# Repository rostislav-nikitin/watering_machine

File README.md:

# Watering machine

Watering machine is a device that control a watering of the garden. This particular machine provides sequential zones watering. This was made to avoid low watering pressure that can happens in case of the parallel mode zone watering.

This device is a control unit with outputs to the external valves - one per watering zone.

<!-- -->

## Modes
The device is designed to work in a two primary modes.

**Normal watering mode**

Used for the regular day-by-day watering. Each zone watering time interval set by the particular zone settings.

**Service mode**

Used for the system blowing before the coservation.
Usually in this mode pump provides an air instead of water. In this case switching to the next zone should be done manually. Through the control button/external input instead of zones watering interval time settings.

According to this, some of button has a different functions depends on the current mode and device state.

## Device logical structure
* [PCB 3D view](#pcb-3d-view "PCB 3D view")
* [Inputs](#Inputs "Inputs")
    * [Power inputs](#power-inputs "Power inputs")
	    * [Main power input](#main-power-input "Main power input")
		    * [Internal low-voltage circuits powering](#internal-low-voltage-circuits-powering "Internal low-voltage circuits powering")
            * [Valves powering](#valves-powering "Valves powering")
        * [Batteries bay](#batteries-bay "Batteries bay")
    * [Logical inputs](#logical-inputs "Logical inputs")
	    * [Control buttons](#control-buttons "Control buttons")
	    * [24 hours internal timer](#24-hours-internal-timer "24 hours internal timer")
	    * [External inputs](#external-inputs)
	        * [External TTL-levels input](#external-ttl-levels-input "External TTL-levels input")
		    * [External rain sensor input](#external-rain-sensor-input "External rain sensor input")
* [Outputs](#outputs "Outputs")
	* [State indicators](#state-indicators "State indicators")
	* [Valves outputs](#valves-outputs "Valves outputs")
	* [Cascading output (not implemented yet)](#cascading-output "Cascading output (not implemented yet)")

## PCB 3D view

<!--  -->

## Inputs

### Power inputs

#### Main power input

This device can be powered by the 9-36 VAC / 500 mA+ power supply.
Power supply characteristics should be calculated by a next formula:

Power supply voltage = valve voltage. Accepted range: [9 VAC - 36 VAC].

Power supply minimal current = 500 mA (internal circuits) + valve maximal current. Accepterd range: [500 mA - 2 A].

##### Internal low-voltage circuits powering
To power input low-voltage circuits was used primary power supply through current rectification and stabilisation. There is +5 VDC powering used for the low-voltage TTL circuits.
* U = +5 VDC (+/- 5%)
* I <= 700 mA

##### Valves powering
Valves solenoids are powering directly from the [main power input](#main-power-input "Main power input") through triacs without any stabilization or transformation.

#### Batteries bay
Battery powering is consists of the battery bay & controller which control charge level/charge batteries. It powers only chips required to run internal time and store device 24 hours timer state. Because they should be invariant for the external power outages.
Ther was used battery bay for 2x18650 battries. Bacause each battery voltage is 3.8-4.2 VDC. And if they are connected sequetely then they provides ~8 VDC voltage. Which is enough to provide +5 VDC after the stabilization.

### Logical inputs

#### Control buttons
Control buttons should be used to set the current watering mode, zone watering time intervals and change the device state - start, stop watering, switch to the next zone manually.

##### Mode switch button

This button toggle normal watering mode / service mode.

##### Start/Stop/Next button

_In the normal watering mode_

In this mode Start/Stop/Next button works in a Start/Stop toggle mode. When device not in a progress state and rain sensor circuit is disonnected then it start watering. Otherwise if device is in progress then stop.

_In the serivce mode_

In this mode Start/Stop/Next button works in a Start->Next->Stop mode. When watering is stopped then this button starts it in case rain sensor circuit is disconnected. On the next push it switch watering zone to the next one. On push when the last zone is in progress it stops the watering.

##### Timer On/Off switch button

This button toggle [24 hours internal timer](#24-hours-internal-timer "24 hours internal timer") on/off.

##### Zone watering time interwal switch

Each zone watering time can be set with a 3 minutes percision.

There are 2 x 5-position sliding switches per zone. One for the rough setup and one for the fine setup. The total zone watering time interval is a sum of rough and fine values.

_Rough setup 5-position sliding switch_

Positions: [1] - 0 minutes, [2] - 15 minutes, [3] - 30 minutes, [4] - 45 minutes, [5] - 60 minutes

_Fine setup 5-position sliding switch_

Positions: [1] - 0 minutes, [2] - 3 minutes, [3] - 6 minutes, [4] - 9 minutes, [5] - 12 minutes

Example: If rough switch in a position [3] (30 minutes) and fine switch in a position [4] (9 minutes) then zone time interval is equal to the  30 minutes + 9 minutes = 39 minutes

#### 24 hours internal timer
24 hours internal timer is used to start watering each 24 hours with everyday recuring.

Timer On/Off button toggle timer function.

##### Watering start time setup
Watering start time could be setup only in normal watering model. This can be made through a manual start watering by the pressing a start/stop/next or by external TTL-levels input high signal. And after the 24 hours it will starts watering again if device is not in a progress state and rain sensor circuit is disconnected.

#### External inputs

##### External TTL-levels input
The external TTL-levels input behaviour is a same as [Start/Stop/Next button](#start/stop/next-button "Start/Stop/Next button") behaviour. Each high TTL level toggle watering state depends on the current mode and the rain sensor circuit conection state.

##### External rain sensor input
It can be used to connect external rain sensor. Rain sensor shold connect both connector pins on rain begins and disconnect on rain ends. When pins are connected then watering is blocking with a maximal priority - no one signal can start watering.
If it connects pins when watering was is in progress then watering stops. And starts only when next start signal comes in case if rain sensor connector pins will be disconnected. 

## Outputs

### State indicators
* Power indicator: 
    * Off if device powered off
    * On if device is powered on
* Mode indicator: 
    * Off if device is in normal watering mode
    * On if device is in service mode
* In progress indicator:
    * Off if device in suspend mode (waiting for the start watering signal)
    * On if watering is in progress
* Zone watering in progress indicator. Each zone has own it's one:
    * Off if a current zone watering not is in progress state
    * On if a current zone watering is in progress state
* Rain indicator:
    * Off if rain sensor circuit is disconnected
    * On if rain sensor circuit is connected
* Change battery indicator:
    * Off if battery in a good state
    * Flashes if battery is corrupted and need replacement

### Valves outputs
There are ouptuts with [valves powering](#valves-powering "Valves powering"). At the moment only one output is active, according to the current watering zone.

### Cascading output
On last zone watering finish there is raises short high-level TTL impulse to cascade next watering device in watering devices sequence.

## Links
Watering machine intro and description on my YouTube channel:

## Contacts
e-mail: rostislav.nikitin@gmail.com

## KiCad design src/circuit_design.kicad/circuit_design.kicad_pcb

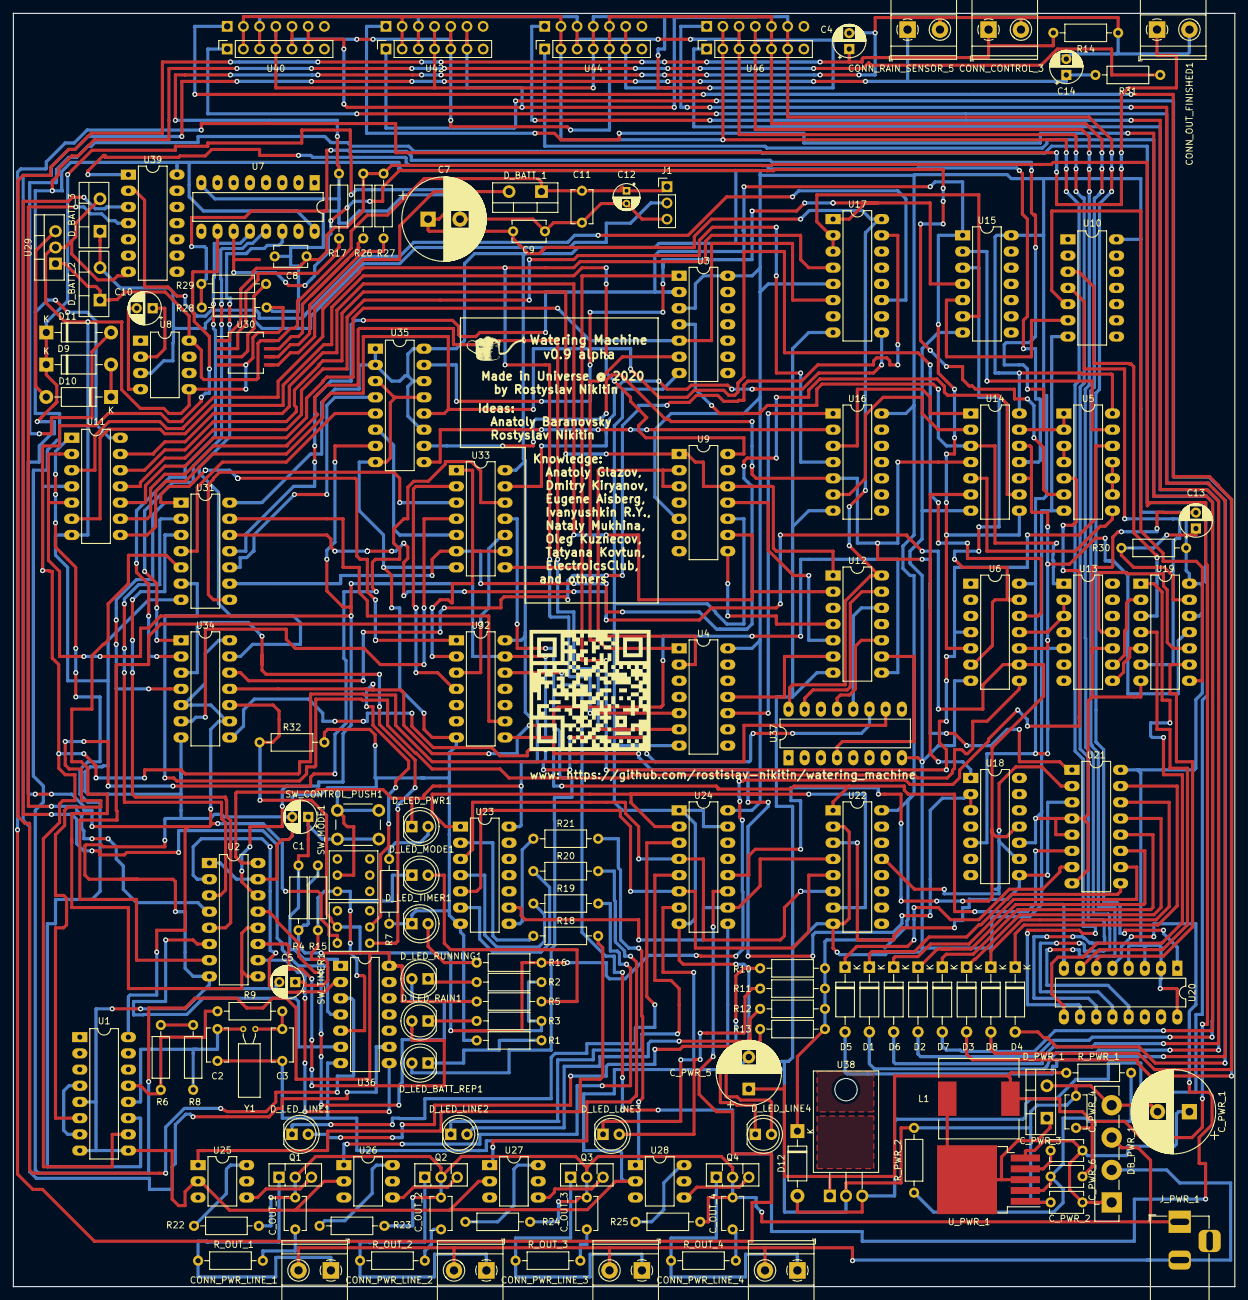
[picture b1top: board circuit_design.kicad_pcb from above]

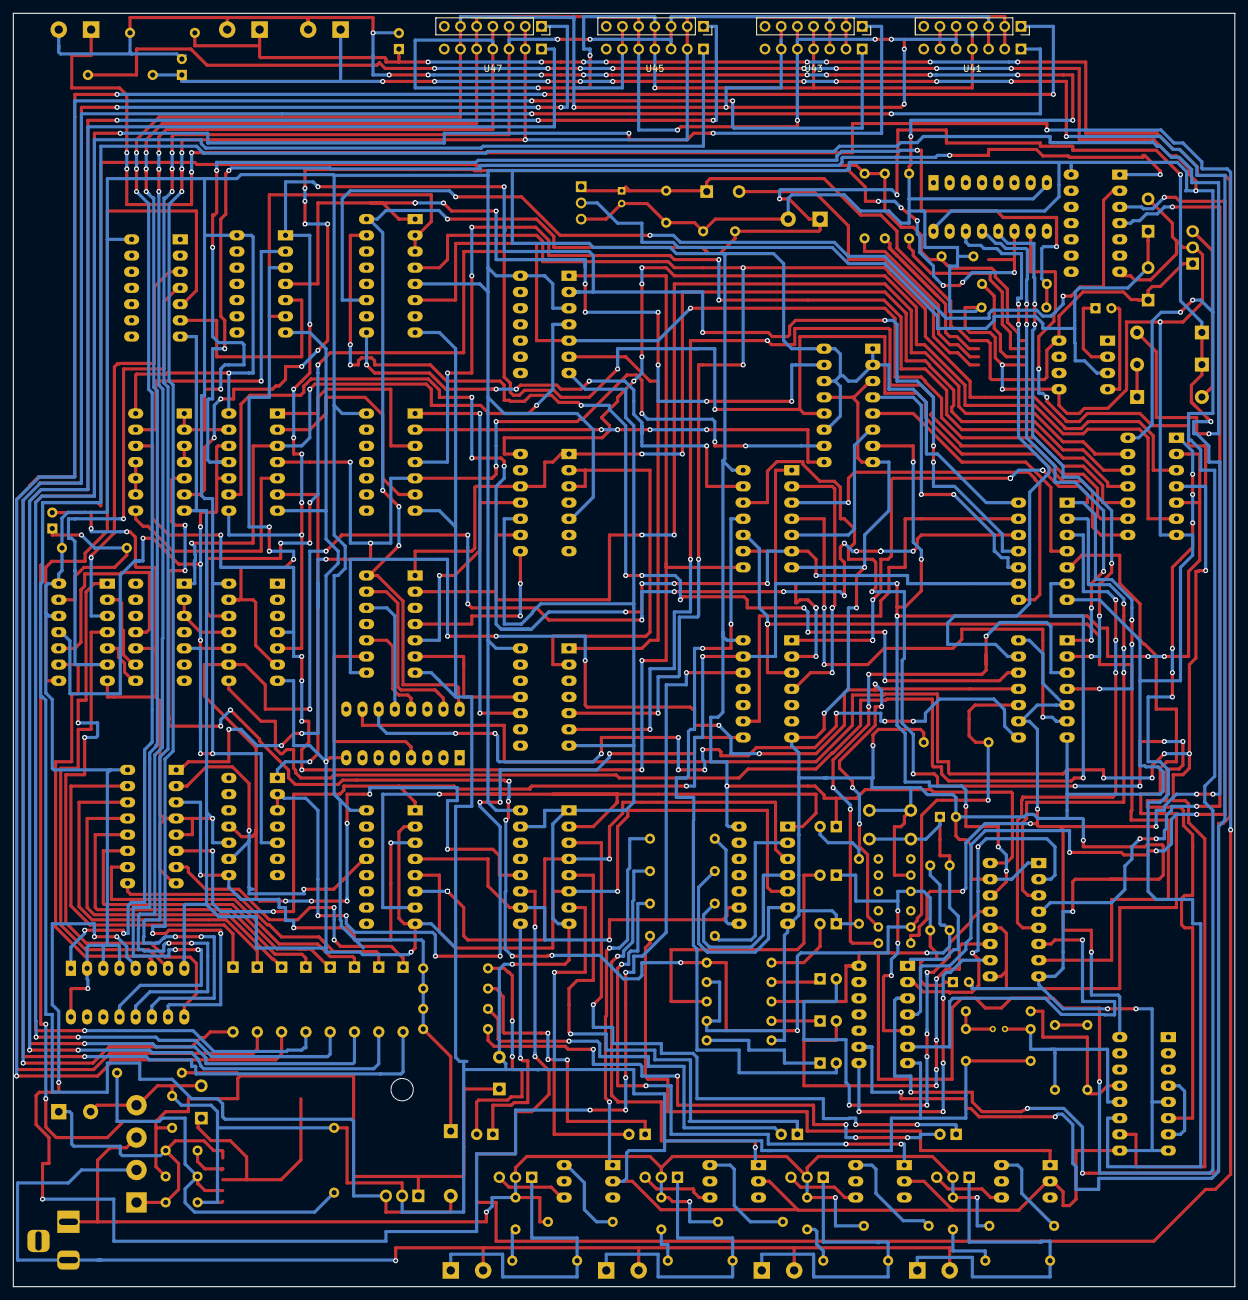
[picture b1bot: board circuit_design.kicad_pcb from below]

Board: 2 copper layers, 191.5 x 199.6 mm, 154 parts (4 on the bottom side), 186 nets.

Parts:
C1, C4, C5, C13, C14: 100uF; CP_Radial_D5.0mm_P2.50mm
C2: 62pF; C_Disc_D5.1mm_W3.2mm_P5.00mm
C3: 22pF; C_Disc_D5.1mm_W3.2mm_P5.00mm
C7: 1000uF; CP_Radial_D13.0mm_P5.00mm
C8, C11: 100nF; C_Disc_D5.1mm_W3.2mm_P5.00mm
C9: 105; C_Disc_D5.1mm_W3.2mm_P5.00mm
C10: 10uF/16V; CP_Radial_D5.0mm_P2.50mm
C12: 22uF/16V; CP_Radial_D4.0mm_P2.00mm
CONN_CONTROL_3: Conn_01x02_Male; TerminalBlock_Phoenix_MKDS-1,5-2-5.08_1x02_P5.08mm_Horizont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
CONN_OUT_FINISHED1: Conn_01x02_Male; TerminalBlock_Phoenix_MKDS-1,5-2-5.08_1x02_P5.08mm_Horizont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
CONN_PWR_LINE_1, CONN_PWR_LINE_2, CONN_PWR_LINE_3, CONN_PWR_LINE_4: Conn_01x02_Male; TerminalBlock_Phoenix_MKDS-1,5-2-5.08_1x02_P5.08mm_Horizont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
CONN_RAIN_SENSOR_5: Conn_01x02_Male; TerminalBlock_Phoenix_MKDS-1,5-2-5.08_1x02_P5.08mm_Horizont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
C_OUT_1, C_OUT_2, C_OUT_3, C_OUT_4: 103; C_Disc_D5.1mm_W3.2mm_P5.00mm
C_PWR_1: 1000 uF/50V; CP_Radial_D13.0mm_P5.00mm
C_PWR_2, C_PWR_3, C_PWR_4: 105; C_Disc_D5.1mm_W3.2mm_P5.00mm
C_PWR_5: 330 uF/50V; CP_Radial_D10.0mm_P5.00mm
C_PWR_6: 333; C_Disc_D5.1mm_W3.2mm_P5.00mm
D1, D2, D3, D4, D5, D6, D7, D8: 1N5817; D_A-405_P10.16mm_Horizontal
D9, D11, D12: 1N4007; D_DO-41_SOD81_P10.16mm_Horizontal
D10: 1N5817; D_DO-41_SOD81_P10.16mm_Horizontal
DB_PWR_1: RS207; Diode_Bridge_Vishay_GBL
D_BATT_1, D_BATT_2, D_BATT_3: SS24T3G; TO-220-2_Vertical
D_LED_BATT_REP1: LED; LED_D5.0mm
D_LED_LINE1, D_LED_LINE2, D_LED_LINE3, D_LED_LINE4: LED; LED_D5.0mm
D_LED_MODE1: LED; LED_D5.0mm
D_LED_PWR1: LED; LED_D5.0mm
D_LED_RAIN1: LED; LED_D5.0mm
D_LED_RUNNING1: LED; LED_D5.0mm
D_LED_TIMER1: LED; LED_D5.0mm
D_PWR_1: MBR745; TO-220-2_Vertical
J1: CONN_BAT; PinHeader_1x03_P2.54mm_Vertical
J_PWR_1: Barrel_Jack; BarrelJack_Horizontal
L1: 47 uH/5A; L_12x12mm_H6mm
Q1, Q2, Q3, Q4: BT134-600E; TO-126-3_Vertical
R1: 200; R_Axial_DIN0207_L6.3mm_D2.5mm_P10.16mm_Horizontal
R2, R3, R5, R7, R10, R11, R12, R13: 270Ohm; R_Axial_DIN0207_L6.3mm_D2.5mm_P10.16mm_Horizontal
R4, R14, R15, R22, R23, R24, R25, R31: 1KOhm; R_Axial_DIN0207_L6.3mm_D2.5mm_P10.16mm_Horizontal
R6, R8: 10MOhm; R_Axial_DIN0207_L6.3mm_D2.5mm_P10.16mm_Horizontal
R9: 510KOhm; R_Axial_DIN0207_L6.3mm_D2.5mm_P10.16mm_Horizontal
R16: 270; R_Axial_DIN0207_L6.3mm_D2.5mm_P10.16mm_Horizontal
R17, R27, R30: 10K; R_Axial_DIN0207_L6.3mm_D2.5mm_P10.16mm_Horizontal
R18, R19, R20, R21: 100 Ohm; R_Axial_DIN0207_L6.3mm_D2.5mm_P10.16mm_Horizontal
R26: 0.5R; R_Axial_DIN0207_L6.3mm_D2.5mm_P10.16mm_Horizontal
R28: 500R; R_Axial_DIN0207_L6.3mm_D2.5mm_P10.16mm_Horizontal
R29: 400R; R_Axial_DIN0207_L6.3mm_D2.5mm_P10.16mm_Horizontal
R32: 1 KOhm; R_Axial_DIN0207_L6.3mm_D2.5mm_P10.16mm_Horizontal
R_OUT_1, R_OUT_2, R_OUT_3, R_OUT_4: 39; R_Axial_DIN0207_L6.3mm_D2.5mm_P10.16mm_Horizontal
R_PWR_1: 15K; R_Axial_DIN0207_L6.3mm_D2.5mm_P10.16mm_Horizontal
R_PWR_2: 2.4 K; R_Axial_DIN0207_L6.3mm_D2.5mm_P10.16mm_Horizontal
SW_CONTROL_PUSH1: SW_DPST_x2; SW_PUSH_6mm
SW_MODE1: SW_DPDT_x2; PB22E09
SW_TIMER1: SW_DPDT_x2; PB22E09
U1: К176ИЕ12; DIP-16_W7.62mm_LongPads
U2, U24: К155ЛП10; DIP-16_W7.62mm_LongPads
U3: К155ЛЕ3; DIP-14_W7.62mm_LongPads
U4, U15, U23, U32, U39: К155ЛН1; DIP-14_W7.62mm_LongPads
U5: К155ЛА3; DIP-14_W7.62mm_LongPads
U6, U14: К155ЛЛ1; DIP-14_W7.62mm_LongPads
U7, U37: 4020; DIP-16_W7.62mm_LongPads
U8: ICL7660; DIP-8_W7.62mm_LongPads
U9, U13, U18: К155ИЕ5; DIP-14_W7.62mm_LongPads
U10, U34: К155ЛА4; DIP-14_W7.62mm_LongPads
U11, U16, U33: К155ЛИ1; DIP-14_W7.62mm_LongPads
U12: К155ЛА1; DIP-14_W7.62mm_LongPads
U17, U35: К155ТВ15; DIP-16_W7.62mm_LongPads
U19: К155ЛП5; DIP-14_W7.62mm_LongPads
U20: К155ИВ1; DIP-16_W7.62mm_LongPads
U21: К155ИД7; DIP-16_W7.62mm_LongPads
U22: К155ИД4; DIP-16_W7.62mm_LongPads
U25, U26, U27, U28: MOC3062M; DIP-6_W7.62mm_LongPads
U29: LM7806_TO220; TO-220-3_Vertical
U30: SC6038; SO-8_5.3x6.2mm_P1.27mm
U31: К155ЛЕ1; DIP-14_W7.62mm_LongPads
U36: К155ТЛ2; DIP-14_W7.62mm_LongPads
U38: LM7806_TO220; TO-220-3_Horizontal_TabDown
U40, U41, U42, U43, U44, U45, U46, U47: SPFT_Sliding_Switch; PinSocket_1x07_P2.54mm_Vertical
U_PWR_1: XL4015; TO-263-5_TabPin3
Y1: 32768; Crystal_C38-LF_D3.0mm_L8.0mm_Horizontal

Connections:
+5V: D12.1, D_LED_PWR1.1, R4.1, R5.1, R10.2, R11.2, R12.2, R13.2, R15.1, R30.1, R31.1, U2.16, U3.3, U3.14, U4.14, U5.14, U6.14, U7.16, U9.5, U10.14, U11.14, U13.5, U14.14, U15.14, U16.14, U17.5, U18.5, U19.12, U19.14, U20.2, U20.3, U20.4, U20.16, U21.16, U22.16, U23.14, U24.16, U31.14, U32.14, U33.14, U35.1, U35.2, U35.11, U35.14, U35.16, U36.14, U39.14
+9V: C8.1, C_PWR_4.1, C_PWR_5.1, C_PWR_6.1, L1.2, R26.1, R27.1, R_PWR_1.1, U30.1, U38.1
/Comparison.Equal: U15.6, U17.2, U17.3
/Completed(In): U6.8, U31.6
/Conn_Control_Raw: C4.1, CONN_CONTROL_3.1, R14.1, U36.3
/Control(Ext.2): U2.4, U39.4
/Control(Ext.): U2.2, U36.2
/Control(In1): U2.3, U31.2
/Control(In2): U2.5, U31.3
/D0: U20.10, U40.2, U41.2, U42.2, U43.2, U44.2, U45.2, U46.2, U47.2
/D1: U20.11, U40.3, U41.3, U42.3, U43.3, U44.3, U45.3, U46.3, U47.3
/D2: U20.12, U40.4, U41.4, U42.4, U43.4, U44.4, U45.4, U46.4, U47.4
/D3: U20.13, U40.5, U41.5, U42.5, U43.5, U44.5, U45.5, U46.5, U47.5
/D4: U20.1, U40.6, U41.6, U42.6, U43.6, U44.6, U45.6, U46.6, U47.6
/Mem.Comparison.Equal: U3.5, U11.10, U17.6
/Mode(Ext.): U2.6, U36.6
/Mode(In): U2.7, U32.3, U33.10
/Mode_Raw: C5.1, D_LED_MODE1.1, R15.2, SW_MODE1.3, U36.5
/Next(Out): U3.1, U5.12, U6.4, U33.8
/Rain(In): U2.9, U2.12, U31.5
/Rain(Led): D_LED_RAIN1.2, U2.11
/Rain_Sensor(Ext.): U2.10, U36.8
/Rain_Sensor_Raw: C14.1, CONN_RAIN_SENSOR_5.1, R31.2, U36.9
/Reset(Out): U3.2, U6.5, U14.8, U15.1, U31.11
/Running(Led): D_LED_RUNNING1.2, U2.13
/Running(Out): U2.14, U11.2, U11.5, U21.6, U22.1, U32.13, U35.7
/RunningInv(out): U20.5, U32.12
/Timer.End: U3.4, U13.1, U14.3
BATT_OUT_+: C11.1, C12.1, D_BATT_1.1, D_BATT_2.1, J1.1, U8.8, U29.1, U30.8
BATT_OUT_MID: D_BATT_2.2, D_BATT_3.1, J1.2, U8.3
CLK_MIN: U1.10, U7.10, U11.4, U37.10
CLK_SEC: U1.6, U33.12
Finished: U6.9, U18.11, U24.12, U31.12
GND: C1.2, C2.2, C3.2, C4.2, C5.2, C7.2, C8.2, C9.2, C11.2, C12.2, C13.2, C14.2, CONN_CONTROL_3.2, CONN_OUT_FINISHED1.2, CONN_RAIN_SENSOR_5.2, C_PWR_1.2, C_PWR_2.2, C_PWR_4.2, C_PWR_5.2, DB_PWR_1.4, D_BATT_3.2, D_LED_TIMER1.1, D_PWR_1.2, J1.3, R1.1, R2.2, R3.2, R7.2, R14.2, R17.2, R28.1, R32.2, R_PWR_2.2, SW_CONTROL_PUSH1.1, SW_MODE1.2, U1.5, U1.8, U1.9, U2.1, U2.8, U2.15, U3.7, U4.7, U5.7, U6.7, U7.8, U8.5, U9.10, U10.7, U11.7, U12.7, U13.10, U14.7, U15.7, U16.7, U17.8, U18.10, U19.7, U20.8, U21.4, U21.5, U21.8, U22.2, U22.8, U23.7, U24.1, U24.8, U24.15, U25.2, U26.2, U27.2, U28.2, U29.2, U30.4, U31.7, U32.7, U33.7, U34.7, U35.3, U35.8, U35.13, U36.7, U37.8, U38.2, U39.7, U_PWR_1.1
GNDREF: CONN_PWR_LINE_1.2, CONN_PWR_LINE_2.2, CONN_PWR_LINE_3.2, CONN_PWR_LINE_4.2, DB_PWR_1.2, J_PWR_1.2
Init: U6.10, U14.10, U14.12, U19.11
unnamed: C1.1, R4.2, SW_CONTROL_PUSH1.2, U36.1
unnamed: C2.1, R8.2, U1.12, Y1.1
unnamed: C3.1, R9.1, Y1.2
unnamed: C10.1, U8.2
unnamed: C10.2, U8.4
unnamed: C13.1, R30.2, U19.13
unnamed: CONN_OUT_FINISHED1.1, U24.11
unnamed: CONN_PWR_LINE_1.1, Q1.1, R_OUT_1.2
unnamed: CONN_PWR_LINE_2.1, Q2.1, R_OUT_2.2
unnamed: CONN_PWR_LINE_3.1, Q3.1, R_OUT_3.2
unnamed: CONN_PWR_LINE_4.1, Q4.1, R_OUT_4.2
unnamed: C_OUT_1.2, R_OUT_1.1
unnamed: C_OUT_2.2, R_OUT_2.1
unnamed: C_OUT_3.2, R_OUT_3.1
unnamed: C_OUT_4.2, R_OUT_4.1
unnamed: C_PWR_1.1, C_PWR_2.1, C_PWR_3.1, DB_PWR_1.1, U_PWR_1.5
unnamed: C_PWR_3.2, U_PWR_1.4
unnamed: C_PWR_6.2, R_PWR_1.2, R_PWR_2.1, U_PWR_1.2
unnamed: D1.1, U21.9
unnamed: D1.2, U46.1
unnamed: D2.1, U21.11
unnamed: D2.2, U44.1
unnamed: D3.1, U21.13
unnamed: D3.2, U42.1
unnamed: D4.1, U21.15
unnamed: D4.2, U40.1
unnamed: D5.1, U21.7
unnamed: D5.2, U47.1
unnamed: D6.1, U21.10
unnamed: D6.2, U45.1
unnamed: D7.1, U21.12
unnamed: D7.2, U43.1
unnamed: D8.1, U21.14
unnamed: D8.2, U41.1
unnamed: D9.2, D10.1
unnamed: D10.2, U29.3
unnamed: D11.2, D12.2, U38.3
unnamed: D_BATT_1.2, U30.5
unnamed: D_LED_BATT_REP1.1, R1.2
unnamed: D_LED_BATT_REP1.2, U33.11
unnamed: D_LED_LINE1.1, U24.3
unnamed: D_LED_LINE1.2, R13.1
unnamed: D_LED_LINE2.1, U24.5
unnamed: D_LED_LINE2.2, R12.1
unnamed: D_LED_LINE3.1, U24.7
unnamed: D_LED_LINE3.2, R11.1
unnamed: D_LED_LINE4.1, U24.9
unnamed: D_LED_LINE4.2, R10.1
unnamed: D_LED_MODE1.2, R5.2
unnamed: D_LED_PWR1.2, R7.1
unnamed: D_LED_RAIN1.1, R3.1
unnamed: D_LED_RUNNING1.1, R2.1
unnamed: D_LED_TIMER1.2, R16.2
unnamed: D_PWR_1.1, L1.1, U_PWR_1.3
unnamed: Q1.3, U25.4
unnamed: Q2.3, U26.4
unnamed: Q3.3, U27.4
unnamed: Q4.3, U28.4
unnamed: R6.1, R9.2, U1.13
unnamed: R6.2, R8.1
unnamed: R16.1, R32.1, SW_TIMER1.2, U5.5, U34.10
unnamed: R17.1, U30.2
unnamed: R18.1, U23.2
unnamed: R18.2, U25.1
unnamed: R19.1, U23.4
unnamed: R19.2, U26.1
unnamed: R20.1, U23.6
unnamed: R20.2, U27.1
unnamed: R21.1, U23.8
unnamed: R21.2, U28.1
unnamed: R22.1, U25.6
unnamed: R23.1, U26.6
unnamed: R24.1, U27.6
unnamed: R25.1, U28.6
unnamed: R26.2, U30.7
unnamed: R27.2, U30.6
unnamed: R28.2, R29.1, U5.1, U5.2, U14.13
unnamed: R29.2, U30.3
unnamed: SW_TIMER1.5, U12.8, U34.11
unnamed: SW_TIMER1.6, U34.3
unnamed: U1.4, U1.7
unnamed: U1.11, U11.1
unnamed: U3.6, U4.1
unnamed: U4.2, U9.2, U9.3
unnamed: U5.3, U5.4
unnamed: U5.6, U7.11
unnamed: U5.9, U5.10, U5.11
unnamed: U10.3, U19.3
unnamed: U10.4, U19.6
unnamed: U10.5, U19.8
unnamed: U10.6, U15.5
unnamed: U4.5, U11.3, U17.4
unnamed: U9.14, U11.6
unnamed: U6.12, U11.8, U35.12
unnamed: U4.6, U11.9
unnamed: U11.11, U16.4
unnamed: U9.1, U9.12, U11.12, U12.1
unnamed: U9.9, U11.13, U12.2
unnamed: U9.8, U12.4
unnamed: U9.11, U12.5
unnamed: U4.11, U12.6
unnamed: U12.9, U37.4
unnamed: U12.10, U37.13
unnamed: U12.12, U37.12
unnamed: U12.13, U37.15
unnamed: U6.11, U13.2, U13.3
unnamed: U13.8, U19.5
unnamed: U13.9, U19.2
unnamed: U13.11, U19.10
unnamed: U14.1, U16.3
unnamed: U14.2, U16.6
unnamed: U14.4, U16.5, U21.1, U35.10
unnamed: U5.8, U14.5
unnamed: U14.6, U18.1
unnamed: U14.9, U31.9, U33.6
unnamed: U14.11, U39.1
unnamed: U5.13, U15.2
unnamed: U6.6, U6.13, U15.3
unnamed: U15.4, U17.1, U35.15
unnamed: U4.10, U16.1
unnamed: U16.2, U35.9
unnamed: U17.9, U33.13
unnamed: U17.11, U39.2
unnamed: U17.15, U34.12
unnamed: U18.2, U18.3, U32.8
unnamed: U18.8, U21.3, U22.3
unnamed: U18.9, U21.2, U22.13
unnamed: U19.1, U20.9
unnamed: U19.4, U20.7
unnamed: U19.9, U20.6
unnamed: U22.4, U23.9, U24.10
unnamed: U22.5, U23.5, U24.6
unnamed: U22.6, U23.3, U24.4
unnamed: U22.7, U23.1, U24.2
unnamed: U31.1, U32.1, U34.4
unnamed: U31.4, U35.5
unnamed: U31.8, U33.3
unnamed: U31.10, U35.4
unnamed: U31.13, U32.9
unnamed: U32.2, U33.1, U33.9
unnamed: U32.4, U33.2
unnamed: U33.4, U34.6
unnamed: U33.5, U35.6
unnamed: U7.13, U34.1
unnamed: U7.12, U34.2
unnamed: U34.8, U37.11
unnamed: U7.14, U34.13
unnamed: U36.4, U39.3
PWR_ALW: C7.1, C9.1, D9.1, D11.1, SW_TIMER1.3, U1.16, U12.14, U17.16, U34.5, U34.9, U34.14, U37.16
VAC: C_OUT_1.1, C_OUT_2.1, C_OUT_3.1, C_OUT_4.1, DB_PWR_1.3, J_PWR_1.1, Q1.2, Q2.2, Q3.2, Q4.2, R22.2, R23.2, R24.2, R25.2

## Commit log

2019-08-31 Initial commit. Was created a next sections: 01. Documentation. Requirements 02. Documentation. User Manual 03. Case design 04. Digital design (KTechLab) 05. Circuit design (KiCAD 5.X)
2019-08-31 Sketches & STL model was added to the case design.
2019-08-31 Sketches was renamed.
2019-10-03 01. Fixed but with triggers: 1. U35A, U35B: the ^K was reconnected from the +VCC to the GND 2. U17A: the ^K was reconnected without inverter 3. U35B, U17A: the ^R was reconnected with inversion 02. R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
2019-10-03 01. The contacts bounce was fixed (the Shmitt trigger was added) 02. U35A JK-trigger outputs was inverted (to solve power on trigger default true state)
2019-10-23 01. The dynacore lib was updated 01. The К176ИЕ13 element was added 02. The circuit desaign was updated 01. The 24 hours re-start loop module was implemented
2019-10-23 01. The circuit design was updated 01. All the elements was moved inside an accepted area
2019-10-23 01. The circuit design was updated - The 24-hours timer reset was fixed
2019-10-23 01. The circuit design was updated - The 24-hours timer switch was replaced with the connectors
2019-10-24 The circuit design was updated - The +5V USB powering was replaced with the +24V LM317 based powering
2019-10-25 The powering module was updated - The resistors values was updated to provide more stable voltage
2019-10-26 The circuit design was updated - The open-collector output inverted (К155ЛН3) was replace with simple inverter one (К155ЛН1) - The logic powering was update to support AC/DC input voltage (diode brid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
2019-10-28 The circuit design was updated - The capicator and GNDREF was added to the powering module
2019-10-29 The circuit design was updated - The timer reset logic was updated. Now timer resets on watering start instead on button was pressed.
2019-10-29 The circuit design was updated: - Now timer resets on washing starting and button is pressed (to avoid overwrite timer by external source).
2019-11-02 01. The state machine was updated - Reset on complete was switched off. As result the circuit started to work correctly and it design was simplified 02. The 24-hours timer was updated - Push button w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
2019-11-08 01. 24h timer module was fixed. Now on 24h event it circuit already in the 'running' is does not stopping 02. U18 reset was fixed 03. High voltage module (with opto and simple triacs) was added 04. C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
2019-11-15 01. Power module was updated - Main chip was changed from the LM317 to the XL4015 - XLSEMI library was added
2019-11-15 The RC chain was added to the triac high voltage outputs.
2019-11-16 01. CLK connection was changed to release mode (run at 1 KHz instead of 1 Hz) 02. Added inputs filtering capicators
2019-11-16 The output triacs filters components was updated
2019-11-16 Small fixes was made
2019-11-16 Power module was fixed: - Missing drossel was added
2019-11-16 The chip footprint was fixed: - The socket was replaced with header
2019-11-18 The RTC was updated: - The RTC power supply/battery switch was added (to avoid RTC reset on power off) - The capicators was added to the RTC chips power pins (to avoid RTC reset on switching from the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
2019-11-18 01. The Digikey library was added 02. The RTC power supply/battery switch was updated - The battery holder was updated to the Digikey BS-7 one
2019-11-18 01. The dynacore library was update: - The AOP605 P-N channel MOSFETs DIP8 element was added - Some element(s) was refactored 02. The RTC power supply/battery switch was updated: - The two p-channel 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
2019-11-22 Battery support was added
2019-11-23 The power supply was updated: - The voltage was changed to the +9V - The LM0805 was added
    The power supply / battery swith updated:
    - The schema was redesigned
    - The simple batterys was replaced with the rechargable ones
    - The charging controller and the balancer was added
2019-11-23 The circuit design was annotated
2019-11-24 The restricting diode (to avoid battery current cover all the schema) was added.
2019-11-24 Added paraller power supply ~+5V output through diode to the whole circuit.
2019-12-02 01. The small refactoring was done 02. The on-power init by reset module was added
2019-12-02 The diode bridge was updated
2019-12-03 01. Some of chips was updated to ones without common VCC to fix common powerting issue. 02. The PCB layout update was started
2019-12-05 The PCB layout was updated: - AC circuit was located
2019-12-06 The PCB layout was updated: - The battery module was updated
2019-12-07 The PCB layout was updated
2019-12-10 The PCB layout was fixed according to the rules.
2019-12-26 01. The PCB layout was updated 02. The gerber files was updated 03. The README.md was initialized
2019-12-26 The README.md file was updated: - The PCB 3D layout was added
2020-02-22 01. The "Init" signal label was added 02. The "Init" signal was used to reset the running state and the battery timer triggers 03. Shmidt triggers was added to the Control(Ext.2) and Mode(Ext.) inputs
2020-02-22 The "Init" time was increased to x10 times - The "Init" module resistor was updated from the 1K to the 10K
2020-02-24 The Control(Ext.2) input was updated to output by default a "0" signal and accept a TTL input signal: - The inverter between the Shmidt trigger and the Control(Ext.2) was added - The resistor was con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
2020-02-25 The 1N4007 D1-D7 rectifier diodes was changed to the 1N5817 Shottkey ones.
2020-02-26 01. The connectors was placed to the external signals near to chips (to avoid long lines) 02. The LM7806(U38) was put to the board to dissipate heat
2020-02-28 01. The BT136-600E triacs was replaced with the BT134-600E ones 02. The SMD drossel (L=47uH/0.88A) was replaced with the (L=47uH/2.5A) one 03. The board dimensions was decreased: - Width: 220.345 -> 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
2020-02-28 The PCB layout was optimized
2020-02-28 The 24-hours timer JCONN_SW_DPST02_TIMER_1 connector placement was changed (to be much more far from the other inputs).
2020-02-28 The labels was updated: - Was placed outside of the parts - Was situated to be more readable
2020-02-28 The git repository URI and the corresponding QR code was added to the silkography layer.
2020-02-28 The QR code footprint was locked.
2020-02-29 The board size was reduced to the 198.755 mm x 170.815 mm
2020-02-29 Unnecessary elements was removed.
2020-02-29 The PCB layout was updated from the schematic.
2020-02-29 The title labels was aligned.
2020-02-29 01. The unnecessary element was removed 02. The QR code was added
2020-03-05 The timer reset logic was updated. Now it is resetting not by the start button/external signal but on enabed.
2020-03-18 PCB layout was updated
2020-03-19 01. The power module was moved bottom 02. The zone time select jumpers was replaced with sliding switches 03. The zone time select module was moved top 04. The 24-hour timer LED circuit was added
2020-03-20 The PCB was updated to be compartible with KRADEX Z26 box 01. Connectors was replaced with buttons, LEDs and terminal blocks 02. Buttons, LEDs and terminal blocks positioning was updated Out finish s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
2020-03-21 01. The labels positions was updated 02. The diode bridge footprint was updated 03. The drill holes was added/updated
2020-03-21 The back/front mask was removed from the sliding switches holes.
2020-03-21 The high capicator(s) position was updated to create possibility to put them vertically.
2020-03-21 The battery health check watchdog enabling jumper was added. Now device can be configured to use a battery health check watchdog or not.
2020-03-21 The bill of materials was regenerated.
2020-03-22 The battery health check jumper was replaced with a signal from the 24-hours timer on/off button. Now used a next battery health check enabling algorithm: If 24-hours timer is in "on" state then the 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
2020-03-22 01. The knowledge people list was updated: Eugene Aisberg was added 02. The labels positions was updated
2020-04-01 The gerber/drill files was updated.
2020-04-02 The knowledge list was updated
2020-07-05 Update README.md
    Box picture was updated
2020-07-05 Update README.md
    Box image was updated
2020-07-05 Update README.md
    The box image was updated
2020-07-05 Update README.md
    The PCB image was updated
2020-07-05 Update README.md
    The box & PCB images was updated
2020-07-05 Update README.md
    The google links was removed
